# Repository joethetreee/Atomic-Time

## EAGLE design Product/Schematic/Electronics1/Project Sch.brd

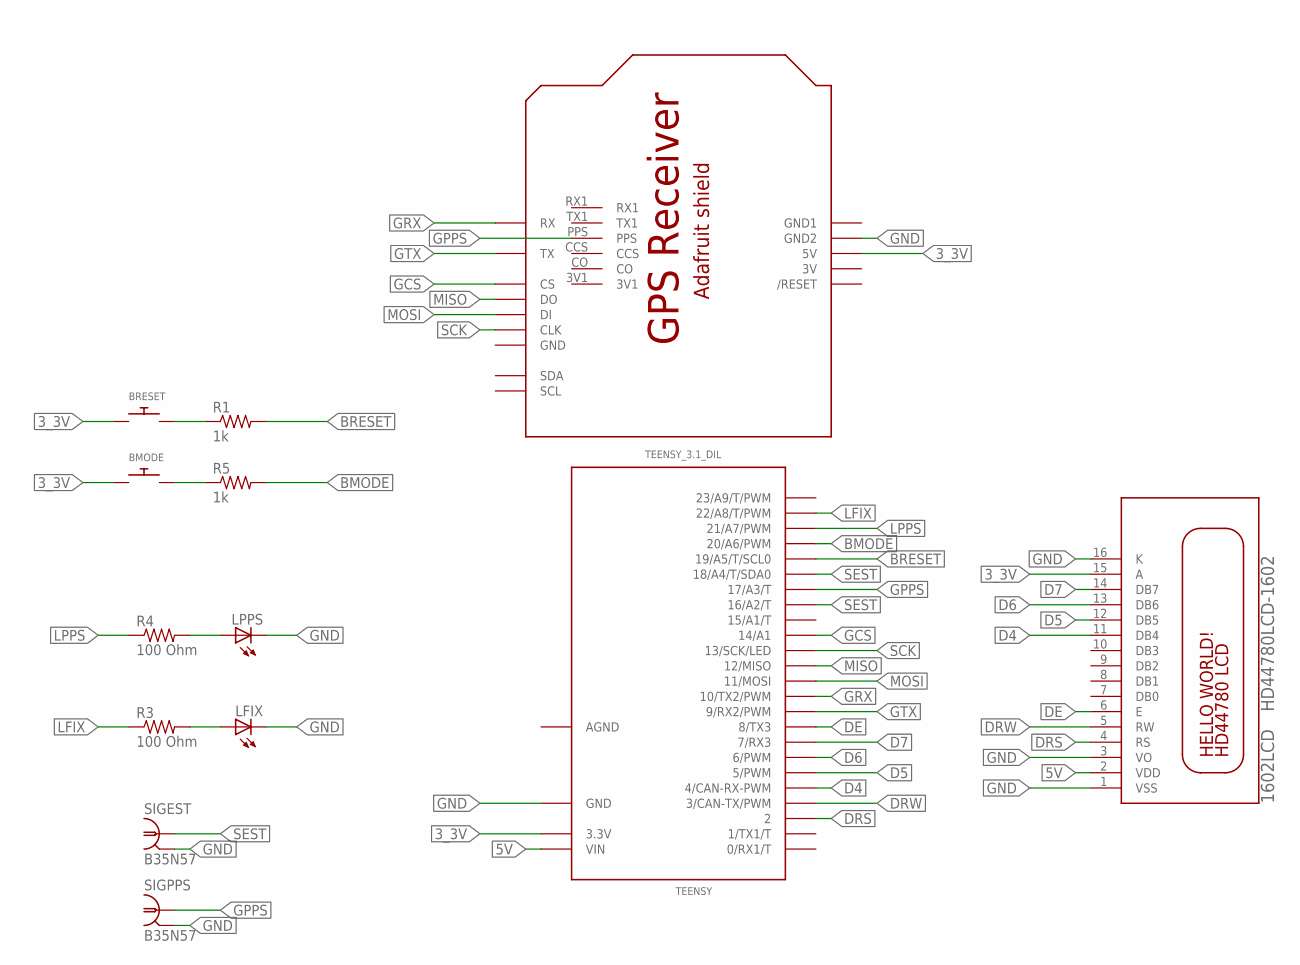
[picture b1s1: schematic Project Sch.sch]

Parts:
1602LCD: HD44780LCD-1602; LCD1602
BMODE: SWITCH_PUSHBUTTONEVQ-PE; TACT_PANA-EVQ
BRESET: SWITCH_PUSHBUTTONEVQ-PE; TACT_PANA-EVQ
LFIX: LED3MM
LPPS: LED3MM
R1, R5: 1k; 0204/7
R3, R4: 100 Ohm; 0204/7
SIGEST: B35N57
SIGPPS: B35N57
TEENSY: TEENSY_3.1_DIL; TEENSY3-DIL
U1: ADAFRUIT_GPS_SHIELD-DIMENSION; ADAFRUIT_GPS_SHIELD

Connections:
3V: U1.3V
3_3V: 1602LCD.15 (A), BMODE.P$1, BRESET.P$1, TEENSY.3.3V, U1.5V
5V: 1602LCD.2 (VDD), TEENSY.VIN
AGND: TEENSY.AGND
BMODE: R5.2, TEENSY.20/A6 (20/A6/PWM)
BRESET: R1.2, TEENSY.19/A5 (19/A5/T/SCL0)
D4: 1602LCD.11 (DB4), TEENSY.4 (4/CAN-RX-PWM)
D5: 1602LCD.12 (DB5), TEENSY.5 (5/PWM)
D6: 1602LCD.13 (DB6), TEENSY.6 (6/PWM)
D7: 1602LCD.14 (DB7), TEENSY.7 (7/RX3)
DE: 1602LCD.6 (E), TEENSY.8 (8/TX3)
DRS: 1602LCD.4 (RS), TEENSY.2
DRW: 1602LCD.5 (RW), TEENSY.3 (3/CAN-TX/PWM)
GCS: TEENSY.14/A0 (14/A1), U1.CS
GND: 1602LCD.1 (VSS), 1602LCD.3 (VO), 1602LCD.16 (K), LFIX.K (C), LPPS.K (C), SIGEST.2, SIGEST.3 (2), SIGEST.4 (2), SIGEST.5 (2), SIGPPS.2, SIGPPS.3 (2), SIGPPS.4 (2), SIGPPS.5 (2), TEENSY.GND, U1.GND, U1.GND2
GND1: U1.GND1
GPPS: SIGPPS.1, TEENSY.17/A3 (17/A3/T), U1.PPS
GRX: TEENSY.10 (10/TX2/PWM), U1.RX
GTX: TEENSY.9 (9/RX2/PWM), U1.TX
LFIX: R3.1, TEENSY.22/A8 (22/A8/T/PWM)
LPPS: R4.1, TEENSY.21/A7 (21/A7/PWM)
MISO: TEENSY.12 (12/MISO), U1.DO
MOSI: TEENSY.11 (11/MOSI), U1.DI
unnamed: BRESET.P$2, R1.1
unnamed: BMODE.P$2, R5.1
unnamed: LFIX.A, R3.2
unnamed: LPPS.A, R4.2
SCK: TEENSY.13 (13/SCK/LED), U1.CLK
SEST: SIGEST.1, TEENSY.16/A2 (16/A2/T), TEENSY.18/A4 (18/A4/T/SDA0)

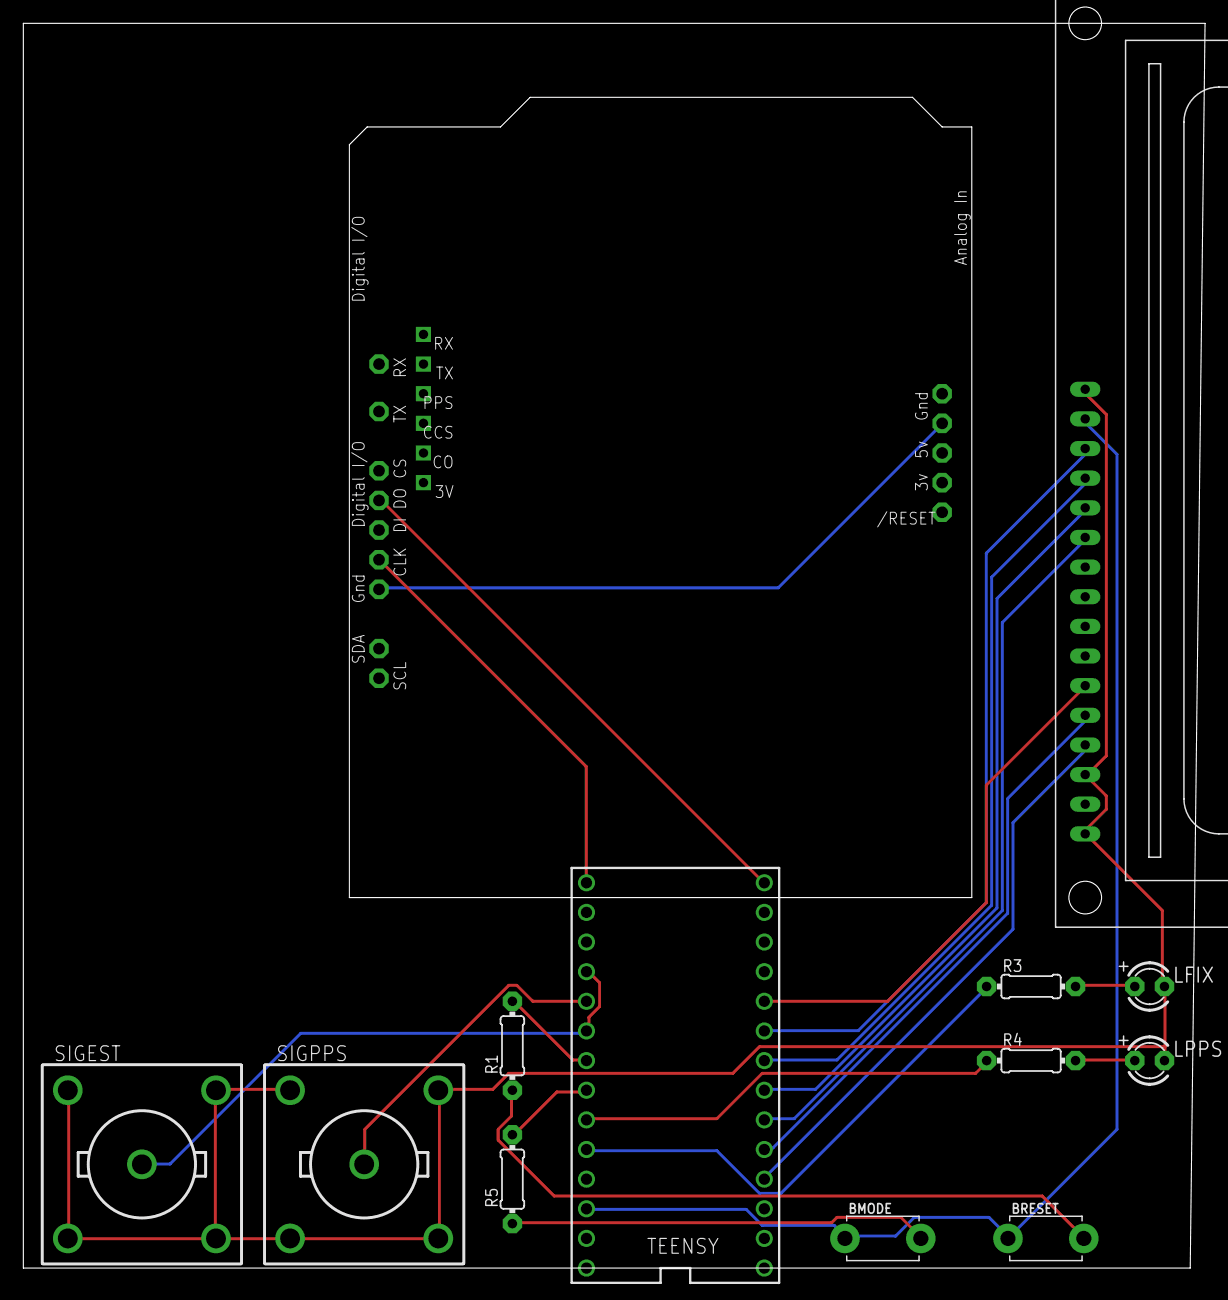
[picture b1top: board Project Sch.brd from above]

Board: 2 copper layers, 101.3 x 106.7 mm, 13 parts (0 on the bottom side), 26 nets.

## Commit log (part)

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2015-10-06 Arduino Time Comparison
    Compares system time to Arduino time.
2015-10-07 Added Arduino code
    Added Arduino program and modified ArduinoDrift.py for compatibility
2015-10-11 Moved GPSDrift related files to separate folder.
    GPSDrift related files were cluttering the main folder when combined
    with results tables. Moved all related files to /GPSDrift/
2015-12-02 Added many files.
    GitHub upload problems hopefully now sorted so have been able to do a
    mass upload.
2015-12-02 Added files that I have made
    Files are in a separate folder called "Duncan"
    There are some duplicates of files already in the github from the start
    of the project
2015-12-05 Minor bug fixes and additions to Interrupt+NMEA
    Fixed interrupt_nmea LED error code by implementing SPI.end() in the
    error function.
    Fixed CorrectJumps.py issue with first data after connecting.
    Before, the data was deemed good/bad based on whether there was a fix.
    However, the PPS typically comes in ~400 ms before the nmea sentences
    (only when there is a fix). If it goes from no fix -> fix in this
2015-12-06 Correlation program (no. of satellites)
    Added program + results from looking at number of satellites with
    pps-ser times
2015-12-07 Changed spaces to tabs
2015-12-07 Fixed Resetting Problem + Commenting
    Fixed a problem where the Arduino would occasionally reset itself due to
    variable memory being filled up. This was accomplished by changing the
    code to not rely on the Adafruit GPS library, and instead use standard
    serial reads.
    Also commented code more thoroughly.
2015-12-09 Revert "Revert "Minor changes to Kalman.py""
    This reverts commit 8196dae8626398836942117c78cfb10692bfd33b.
2015-12-09 Test 2
    Another graph
2015-12-09 another graph
2015-12-09 Changes to ConQual python programs (correlate connection properties to PPS-Serial dt)
    Modified ConQual (connectionQuality) so that it plots a scatter graph
    which works better with large data sets.
    ConQualDist now works with the new data format with NMEA sentences and
    "t<serialTime>,<ppsTime>"
    This plots a distribution coloured by a property e.g. number of
    satellites
2015-12-09 more deltions
2015-12-09 Remainder of results
2015-12-11 Interrupt + NMEA\interrupt_nmea\interrupt_nmea.ino - Fixed buffer overflow causing additional unwanted characters and missing NMEA sentences.
    Interrupt + NMEA\Analysis\MultiPlot\multiPlot.py
    - Added file to plot multiple pieces of GGA data against Serial - PPS time.
2015-12-23 Added analysis files
    AllanVariance0 computes Allan variance
    CompareDist uses distributions of a template and the current data to predict PPS times
    Estimator files are to assess performance of different methods of calculating second length (EstSec contains many quick methods; EstSec by dist is the latest attempt to use distribution width)
2015-12-28 Minor grammar changes
2015-12-31 Added avg, std dev
2015-12-31 Added Baseline/ folder and files
    These attempt to calculate the "baseline", the "phase" of PPS-serial time difference. In their current state they are not very useful; I created it in case it improved the second length estimation. I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
    At the very least it can generate graphs showing the baseline
2015-12-31 Minor change to ConQual.py to improve ylim on graphs
    Major changes to ConQualDist.py to make colouring consistent with that of ConQual.py
2015-12-31 Kalman.py plot comments modified
2015-12-31 Removed unnecessary results files that were left in folders
2016-01-02 My documents for reports
2016-01-02 Added simple program to read serial and save it to text file
2016-01-02 Simple Arduino program to check the Arduino's ability to measure its own time-keeping ability
2016-01-02 Updated programs with consistent plot sizes and relative file names
2016-01-02 Added analysis an results files in separate folder
2016-01-06 Edited for plotting and saving both relevant graphs (PPS-ser and ser-ser)
2016-01-06 Added many new plots, modified some (with consistent styles)
    may contain duplicates with new naming system
2016-01-06 Corrected Std dev for ser-ser (used to be pps-ser)
2016-01-26 Added standard formatting to graphs
2016-01-26 Added choice of start, end of data features
    Corrected title of consecutive PPS message graph
2016-01-26 EstSec by dist.py was unversioned; now adding it to my git
2016-02-10 Updated ArdSaveSerial.py
    this file is for reading and saving serial input to file
    it is used with the Garmin arduino program that does not save to SD
2016-02-10 Allan Var: no significant changes
    Baseline: added in start, stop parameters
    CorrectJumps:
    -> CorrectData.py no significant changes
    -> CorrectJumps.py modified to improve reliability:
    before, data for which PPS time froze but Serial time updated were salvaged. However, this complicated many processes. Now they are removed entirely. This simpler method allows for the calculations o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
    ** Note: The modification to CorrectJumps.py could be applied to all other instances of the program
2016-02-10 Removed text files that should no be there
2016-02-10 Committed Duncan's images.
2016-02-11 Removed leading entry of data which was invalid.
    Distributions changed as a result (including some file names due to a change of the length of data)
2016-02-11 Removed some duplicate data, altered names on other data to match current convention
2016-02-12 Re-worked the CorrectJumps.py file to be consistent with the Garmin version. This is less forgiving than before, and removes more data. The results are better however. The GPSMIL37ChckdCor.txt file i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
2016-02-12 Fixed some issues with Arduino IDE not liking programs (due to folder/filename conflicts)
    Added in code to GAR_interrupt.ino and GAR_interrupt_SD.ino which should solve problem whereby ppsser times were ~500ms rather than ~400ms as they should be. Fixed by ensuring that the NMEA sentences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
    GAR_interrupt.ino has been tested but not GAR_interrupt_SD.ino.
2016-02-19 Script to test Timer0 functionality for a 1x10^-3Hz timer function.
2016-02-19 kalman_ard.ino - Fixed millisecond interrupt crashing the program. - Added 500 millisecond delay to account for late signal arrival.
2016-02-20 kalman_ard.ino - Added timestamp output with 500ms offset.
2016-02-26 kalman_pps_dt.py - Python script to take data format produced by kalman_pps_measure.ino and plot the time difference between data points.
    /results/
    - Added datasets from kalman_pps_measure.ino
2016-02-27 kalman_ard.py - Python script to test out future additions to the kalman_ard.ino Arduino file. - Added basic Kalman filter replicating Arduino Kalman filer. - Added SV number PPS - Ser time delta cor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
2016-02-28 kalman_ard.py - Added Kalman PPS - Kalman PPS time delta graph.
2016-03-03 kalman_pps_dt.py - Added distribution plot of kalman PPS time deltas.
    kalman_ard.ino
    - Added the ability to save Kalman PPS times to SD card for later analysis.
2016-03-09 No real changes to CorrectData.py
    CorrectJumps.py has been updated to be in line with Garmin version. No huge change in performance; instead of subtracting an integer number of 1000 ms from jumps, the jumps are now reset to 1000 ms.
    This works better for big jumps because we don't get "amplification" of the difference over the course of many seconds crammed into a single second. The bad part is that the distribution of PPS-PPS t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
    Both the previous and current methods preserve PPS-serial times though.
2016-03-09 Modified GPSMIL33ChckdCor.txt and GPSMIL37ChckdCor.txt -- these new files were passed through the latest version of CorrectJumps.py _________________________ IMPORTANT: The old Github version of GPSM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
2016-03-11 kalman_ard.ino - Forgot to rest the "firstLoop" variable to True after completing serial read loop.
2016-03-13 kalman_ard.ino - Converted the filterStep() function to mostly use integer arithmetic. This solves the loss of accuracy due to float precision bug mentioned in the previous commit.
2016-03-23 kalman_pps_dt.py - Fixed a possible out-of-bounds error.
2016-03-26 Largely updated to look for + save files in results folder
    KalCor updated so that its second length runs a kalman filter
2016-03-26 Updated a couple of results files
2016-03-27 Added new set of data KL1PRD03.TXT
2016-03-28 Minor fix to spot and remove leading (first) line when it has no fix
2016-03-28 Added results and graphs from oscilloscope recordings
2016-03-29 Moved Interrupt arduino file (minimalistic file used for "checking" that the times measured by the full arduino file were accurate)
    Added data and graphs from Interrupt
    Added new InterruptTrigger files and data
    This is more scientific; InterruptTrigger.ino runs on an arduino and mimics the serial and PPS outputs of the GPS receiver. PPS-serial time differences were
    - measured by the Arduino running InterruptTrigger.ino
    - measured by the teensy running the full box software
    The differences were analysed.
2016-03-29 Added in more analysis code and graphs (these are largely for interest, to see how closely the GPS receiver was mimicked)
2016-03-30 atcgr folder: - Contains LabVIEW files and results + PPS PPS comparison results.
2016-03-31 Added results graphs from sv_offset.py and pps_distro.py
2016-04-01 Corrected file to subtract expected PPS-ser offset when using measurement in Kalman filter (the offset part was commented out)
2016-04-04 Updated Analysis programs
    CorrectJumps has been changed to reset jumps to a random "good" second length rather than to 1000 ms
    Added Stationary_ADF.py which determines whether a time series is stationary
2016-04-04 Added old results from Garmin (not sure how useful these are at this stage)
2016-04-04 Updated Allan deviation plots, including linear
2016-04-04 Updated Allan Var/AllanVariance0.py to plot a shortened linear dataset
2016-04-06 kalman_ard.py - Added statistics print out.
2016-04-06 Another change (mentioned that it would be a good idea in the last change)
    When jumps in PPS are detected they are reset to a sensible second length
    - originally this was 1000 ms (since there weren't too many jumps any inaccuracies would not matter)
    - this affected sensitive timing tests like Allan deviation of PPS so in the last modification the jump was reset to one of the other recorded "good" second lengths in the dataset
    - since the Teensy's clock (or PPS) drifts this meant that not all of the recorded second lengths were appropriate for each jump. Now a second length from a second close to the jump is picked (random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
2016-04-08 Added Segment.py which uses segmented approach to estimate second times
    This uses the simple "block" segment version rather than moving segment
2016-04-08 Removed svg files
    Added segmented analysis data
    txt file format:
    pps,seg,#sat
2016-04-09 Added data for a new real-time Kalman filter which uses a "tighter" Kalman filter
    int satOffsets[12] = {185, 193, 205, 215, 227, 235, 245, 255, 275, 294, 302, 303};
    int satUncerts[12] = {25 , 20 , 20 , 12 , 13 , 13 , 15 , 20 , 21 , 25 , 22 , 20 };
    uint32_t sec_dxp = 999985; // prediction of second length us
    uint32_t sec_up = 1000; // uncertainty in prediction us
2016-04-10 kalman_ard.py - Added standard deviation to distribution plots.
2016-04-10 kalman_ard.ino - Added code to save PPS input time.
2016-04-11 Removed end line.
2016-04-11 Allan Var/AllanVariance0.py - Removed unnecessary plots. - Minor formatting changes.
    kalman_pps.py
    - Added file to plot experimental Kalman data graphs and statistics.
2016-04-11 Updated most plots with new standardised format
2016-04-11 Updated Arduino file with new tight Kalman filter parameters
2016-04-11 Added files which (for some reason) were not saved by git
2016-04-11 Updated plots with latest style convention
